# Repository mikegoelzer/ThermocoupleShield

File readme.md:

# Arduino K-Type Thermocouple Shield

<div align="center">
  
</div>

## Description

Arduino Uno shield designed to interface with K-type thermocouples using the MAX31855 cold-junction compensated thermocouple-to-digital converter.

## Features

- Compatible with Arduino Uno form factor
- Uses MAX31855 for K-type thermocouple interface
- Display screen with Arduino sketch for displaying temperature
- Temperature range: -200°C to +1350°C

## Repository Contents

- `/hardware` - KiCad project files and custom parts
- `/doc` - documentation and images
- `/bom` - bill of materials spreadsheets
- 

## Hardware Requirements

- Arduino Uno or compatible board
- K-type thermocouple
- This shield PCB

## License

This hardware design is released under the [CERN Open Hardware License v2 - Strongly Reciprocal](https://ohwr.org/cern_ohl_s_v2.txt).

## Contributing

Contributions to improve the design are welcome. Please submit issues and pull requests.

# Credits

Circuit inspired by [Adafruit #269](https://www.adafruit.com/product/269)

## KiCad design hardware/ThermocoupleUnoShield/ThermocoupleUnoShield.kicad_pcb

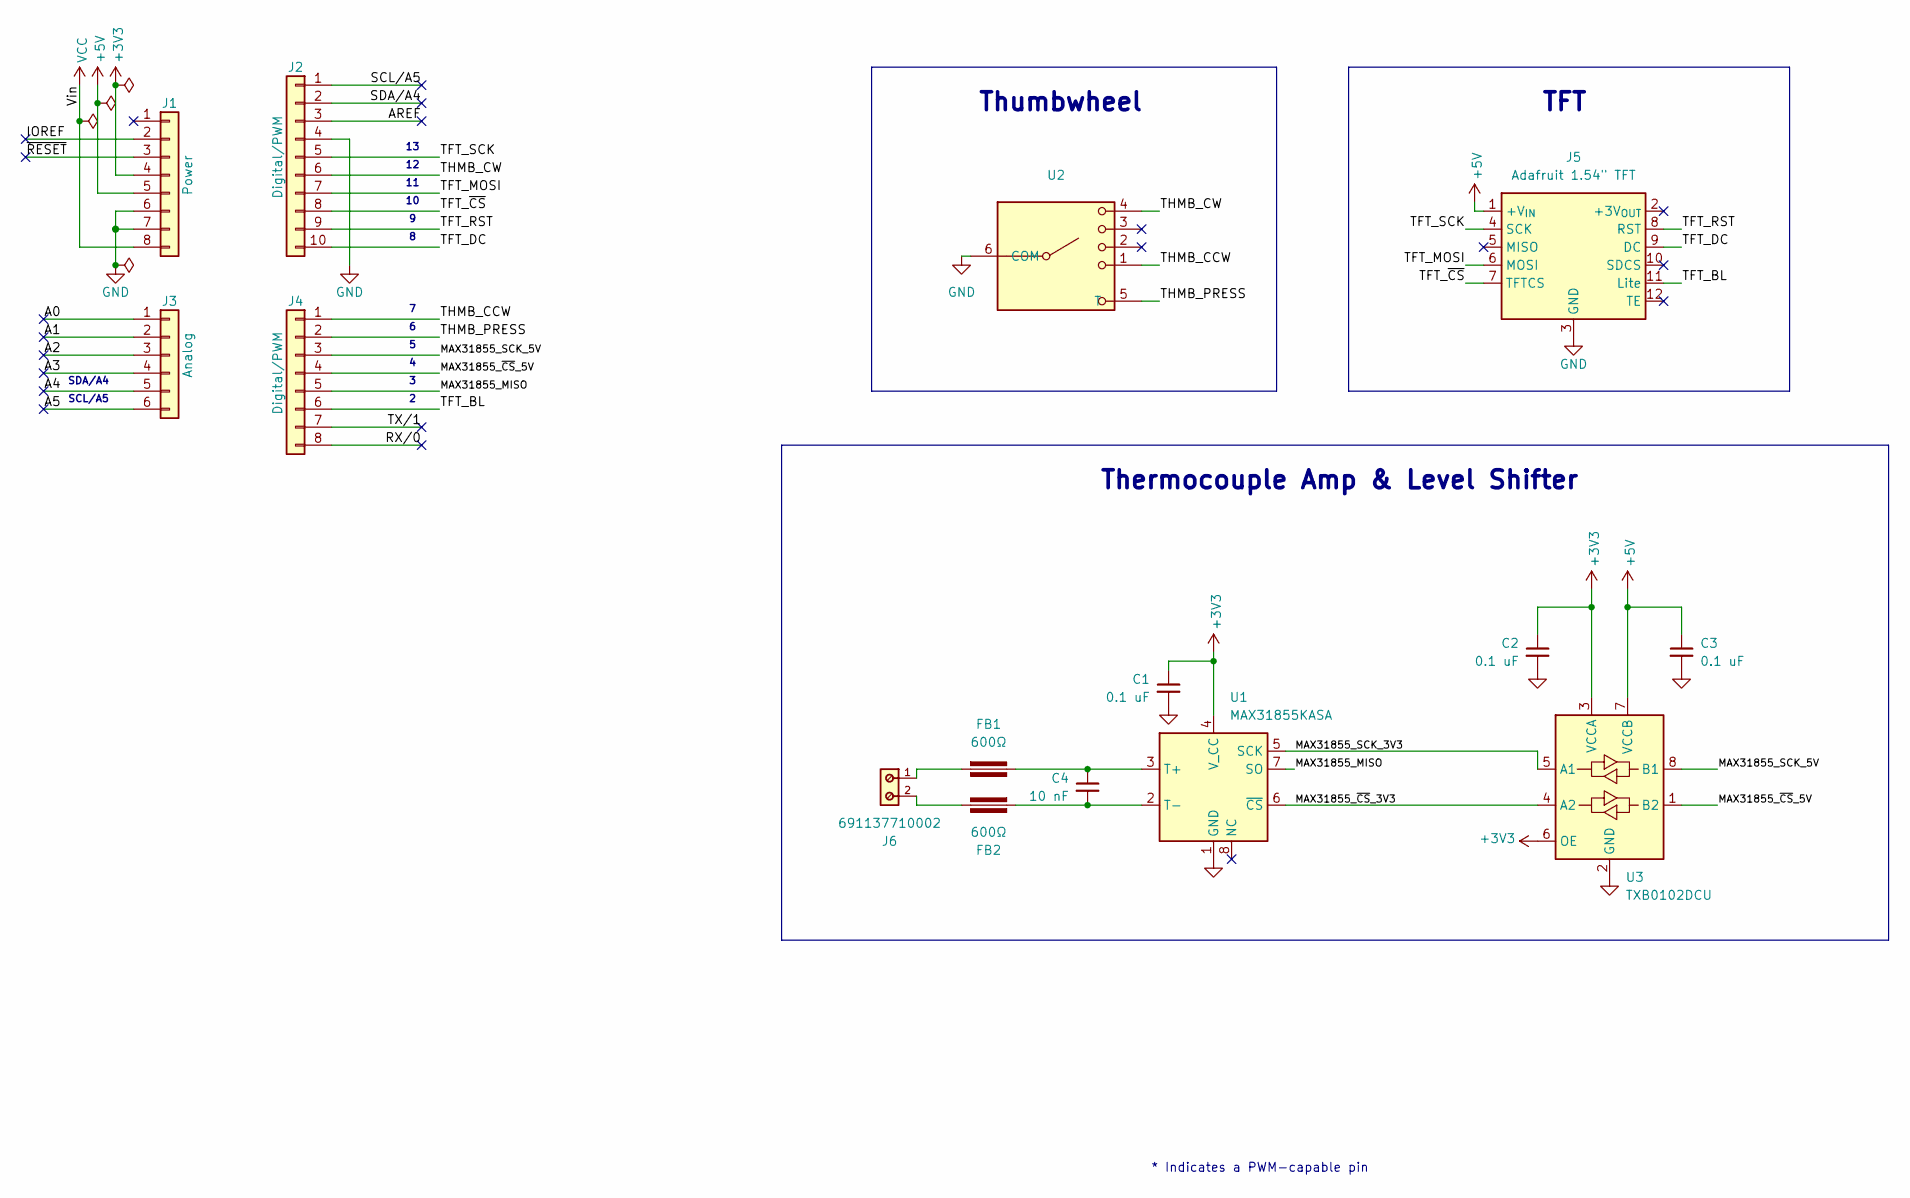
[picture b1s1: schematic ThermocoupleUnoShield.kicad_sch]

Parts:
C1, C2, C3: 0.1 uF; C_0805_2012Metric; MPN CC0805KRX7R9BB104
C4: 10 nF; C_0805_2012Metric; MPN C0805C103K5RACTU
FB1, FB2: 600Ω; Fuse_0805_2012Metric; MPN 74279220601
J1: Power; PinSocket_1x08_P2.54mm_Vertical; MPN SSQ-108-03-F-S
J2: Digital/PWM; PinSocket_1x10_P2.54mm_Vertical; MPN SSQ-110-03-F-S
J3: Analog; PinSocket_1x06_P2.54mm_Vertical; MPN SSQ-106-03-F-S
J4: Digital/PWM; PinSocket_1x08_P2.54mm_Vertical; MPN SSQ-108-03-F-S
J5: Adafruit 1.54" TFT; 1.54 TFT 240x240; MPN 3787
J6: 691137710002; PART-NUMBER 691137710002
U1: MAX31855KASA; SOIC-8_3.9x4.9mm_P1.27mm; MPN MAX31855KASA+T
U2: PLSJ1; MPN PLSJ 1
U3: TXB0102DCU; VSSOP-8_2.4x2.1mm_P0.5mm; MPN TXB0102DCUR

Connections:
+3V3: C1.1, C2.1, J1.4, U1.4 (V_CC), U3.3 (VCCA), U3.6 (OE)
+5V: C3.1, J1.5, J5.1 (+V_{IN}), U3.7 (VCCB)
/A0: J3.1
/A1: J3.2
/A2: J3.3
/A3: J3.4
/A4: J3.5
/A5: J3.6
/AREF: J2.3
/IOREF: J1.2
/MAX31855_MISO: J4.5, U1.7 (SO)
/MAX31855_SCK_3V3: U1.5 (SCK), U3.5 (A1)
/MAX31855_SCK_5V: J4.3, U3.8 (B1)
/MAX31855_~CS_3V3: U1.6 (~CS), U3.4 (A2)
/MAX31855_~CS_5V: J4.4, U3.1 (B2)
/RX/0: J4.8
/SCL/A5: J2.1
/SDA/A4: J2.2
/TFT_BL: J4.6, J5.11 (Lite)
/TFT_DC: J2.10, J5.9 (DC)
/TFT_MOSI: J2.7, J5.6 (MOSI)
/TFT_RST: J2.9, J5.8 (RST)
/TFT_SCK: J2.5, J5.4 (SCK)
/TFT_~CS: J2.8, J5.7 (TFTCS)
/THMB_CCW: J4.1, U2.1
/THMB_CW: J2.6, U2.4
/THMB_PRESS: J4.2, U2.5 (T)
/TX/1: J4.7
/~RESET: J1.3
GND: C1.2, C2.2, C3.2, J1.6, J1.7, J2.4, J5.3 (GND), U1.1 (GND), U2.6 (COM), U3.2 (GND)
unnamed: FB1.1, J6.1
unnamed: FB2.2, J6.2
unnamed: C4.1, FB1.2, U1.3 (T+)
unnamed: C4.2, FB2.1, U1.2 (T-)
VCC: J1.8

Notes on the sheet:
Thumbwheel
TFT
SCL/A5
* Indicates a PWM-capable pin
SDA/A4
Thermocouple Amp & Level Shifter

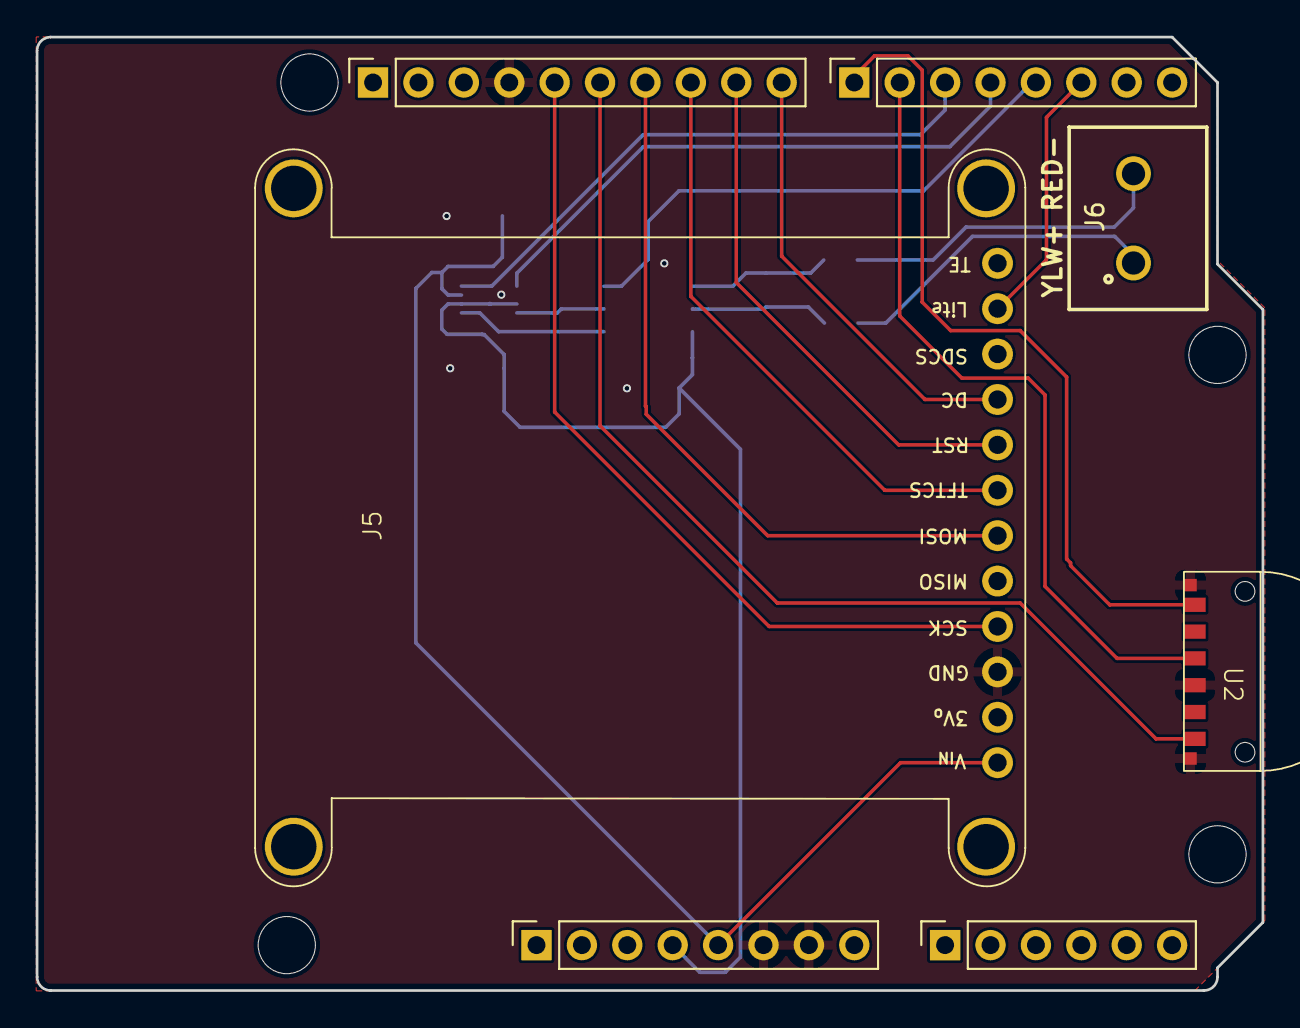
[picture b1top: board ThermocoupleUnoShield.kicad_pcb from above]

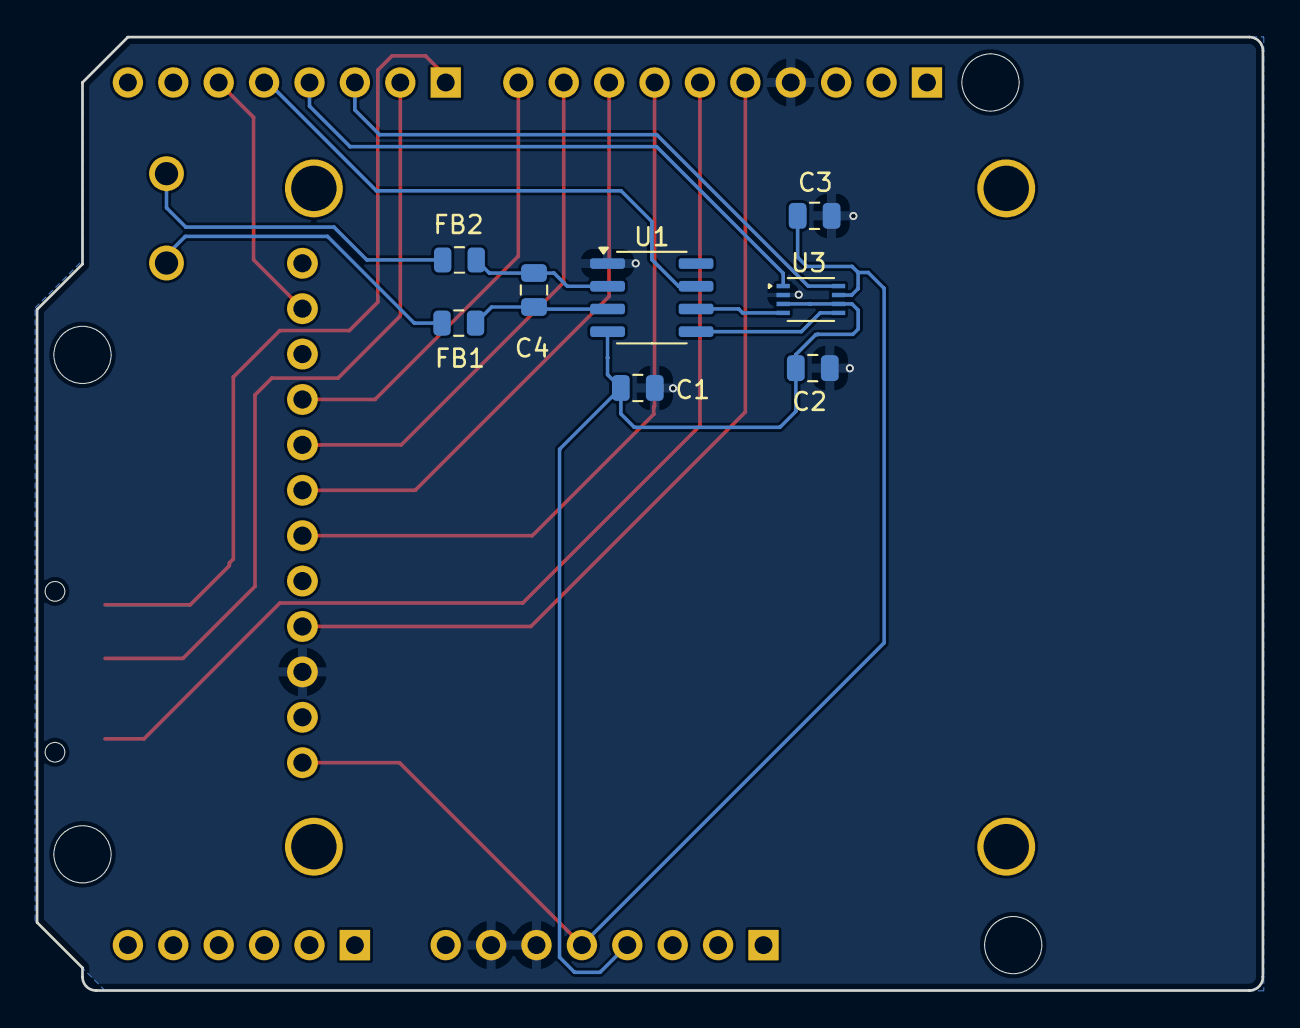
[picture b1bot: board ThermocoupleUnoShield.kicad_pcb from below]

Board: 2 copper layers, 68.6 x 53.3 mm, 19 parts (8 on the bottom side), 21 nets.

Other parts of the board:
MH1, MH2, MH3, MH4: MountingHole_3.2mm

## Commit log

2025-02-13 add cursor workspace file
2025-02-13 add 3d render
2025-02-13 move parts dir under hardware
2025-02-13 rename doc->docs
2025-02-13 add readme.md
2025-02-13 add attribution to adafruit for design idea
